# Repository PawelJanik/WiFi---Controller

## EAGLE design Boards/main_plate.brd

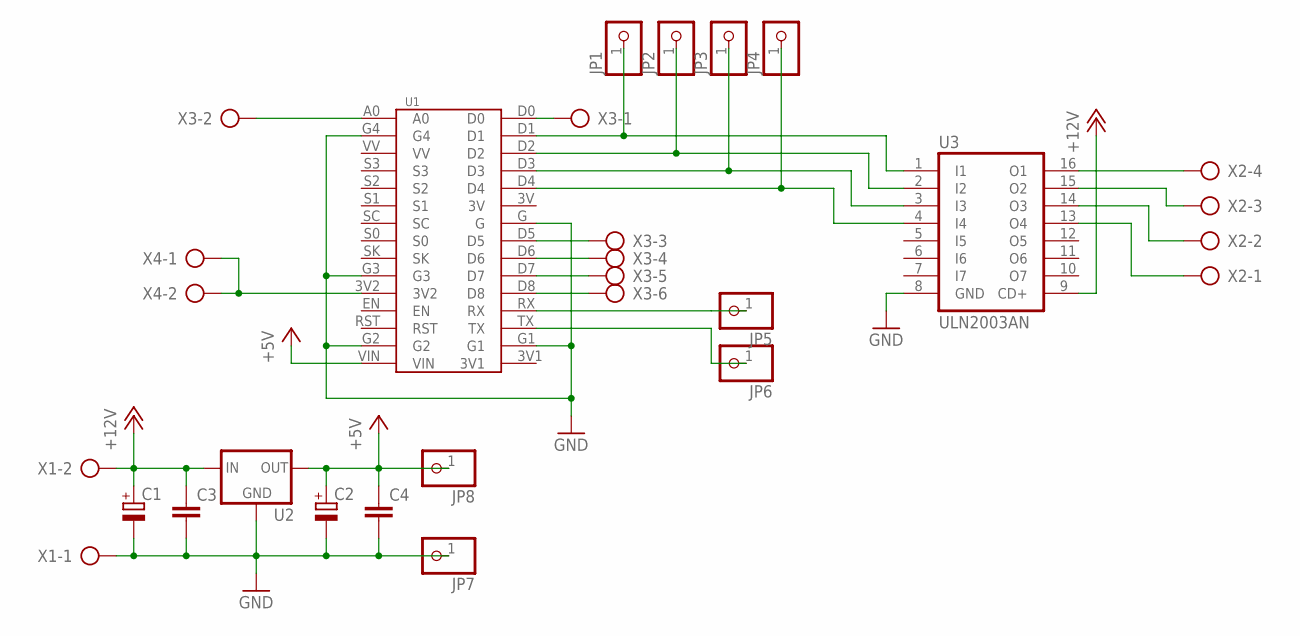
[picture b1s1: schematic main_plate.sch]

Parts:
C1, C2: CPOL-EUE3.5-8; E3,5-8
C3, C4: C-EU025-025X050; C025-025X050
JP1, JP2, JP3, JP4, JP5, JP6, JP7, JP8: PINHD-1X1; 1X01
U1: LOLIN
U2: 78XXS
U3: ULN2003AN; DIL16
X1, X4: AK300/2
X2: AK300/4
X3: AK300/6

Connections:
+5V: C2.+, C4.1, JP8.1, U1.VIN, U2.OUT
+12V: C1.+, C3.1, U2.IN, U3.9 (CD+), X1.2
GND: C1.-, C2.-, C3.2, C4.2, JP7.1, U1.G, U1.G1, U1.G2, U1.G3, U1.G4, U2.GND, U3.8 (GND), X1.1
unnamed: U1.D0, X3.1
unnamed: U3.16 (O1), X2.4
unnamed: U3.15 (O2), X2.3
unnamed: U3.14 (O3), X2.2
unnamed: U3.13 (O4), X2.1
unnamed: U1.D8, X3.6
unnamed: U1.D7, X3.5
unnamed: U1.D6, X3.4
unnamed: JP1.1, U1.D1, U3.1 (I1)
unnamed: JP2.1, U1.D2, U3.2 (I2)
unnamed: JP3.1, U1.D3, U3.3 (I3)
unnamed: JP4.1, U1.D4, U3.4 (I4)
unnamed: U1.D5, X3.3
unnamed: JP5.1, U1.RX
unnamed: JP6.1, U1.TX
unnamed: U1.A0, X3.2
unnamed: U1.3V2, X4.1, X4.2

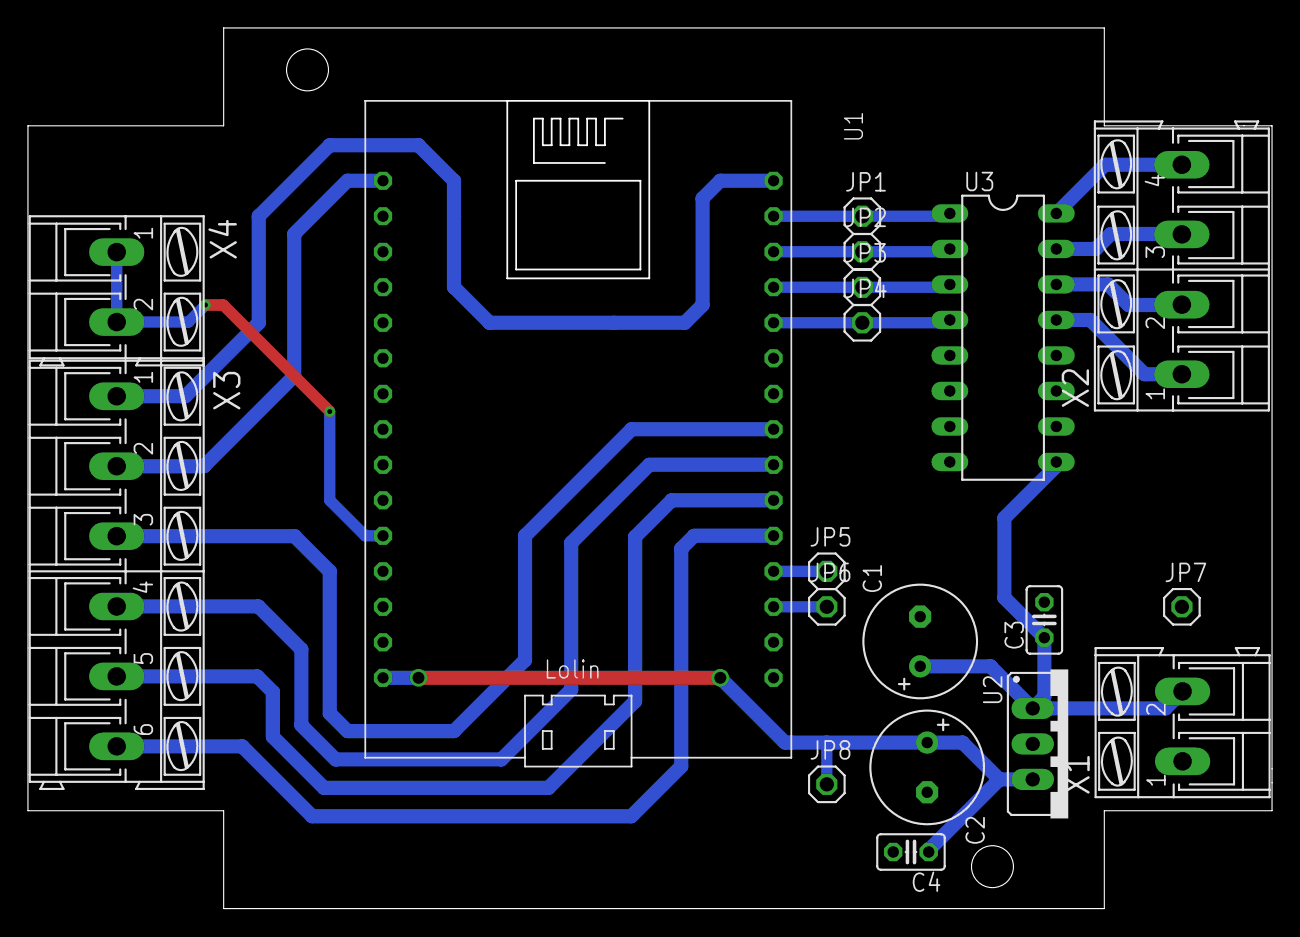
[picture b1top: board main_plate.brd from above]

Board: 2 copper layers, 88.9 x 62.9 mm, 19 parts (0 on the bottom side), 20 nets.

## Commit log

2018-09-16 Electronic schematic and PCB
2018-09-16 add eagle file
2018-11-24 add nodeMCU code
2019-01-03 Normalization of light levels and modification of MQTT topic
    - new ranges of light levels: 0-1000
    - new patern of topic name home/myRoom/light/groupNumber/lightNumber
2019-01-05 Project migration to PlatformIO
2019-02-05 fixed problems with vibration of switch contacts
